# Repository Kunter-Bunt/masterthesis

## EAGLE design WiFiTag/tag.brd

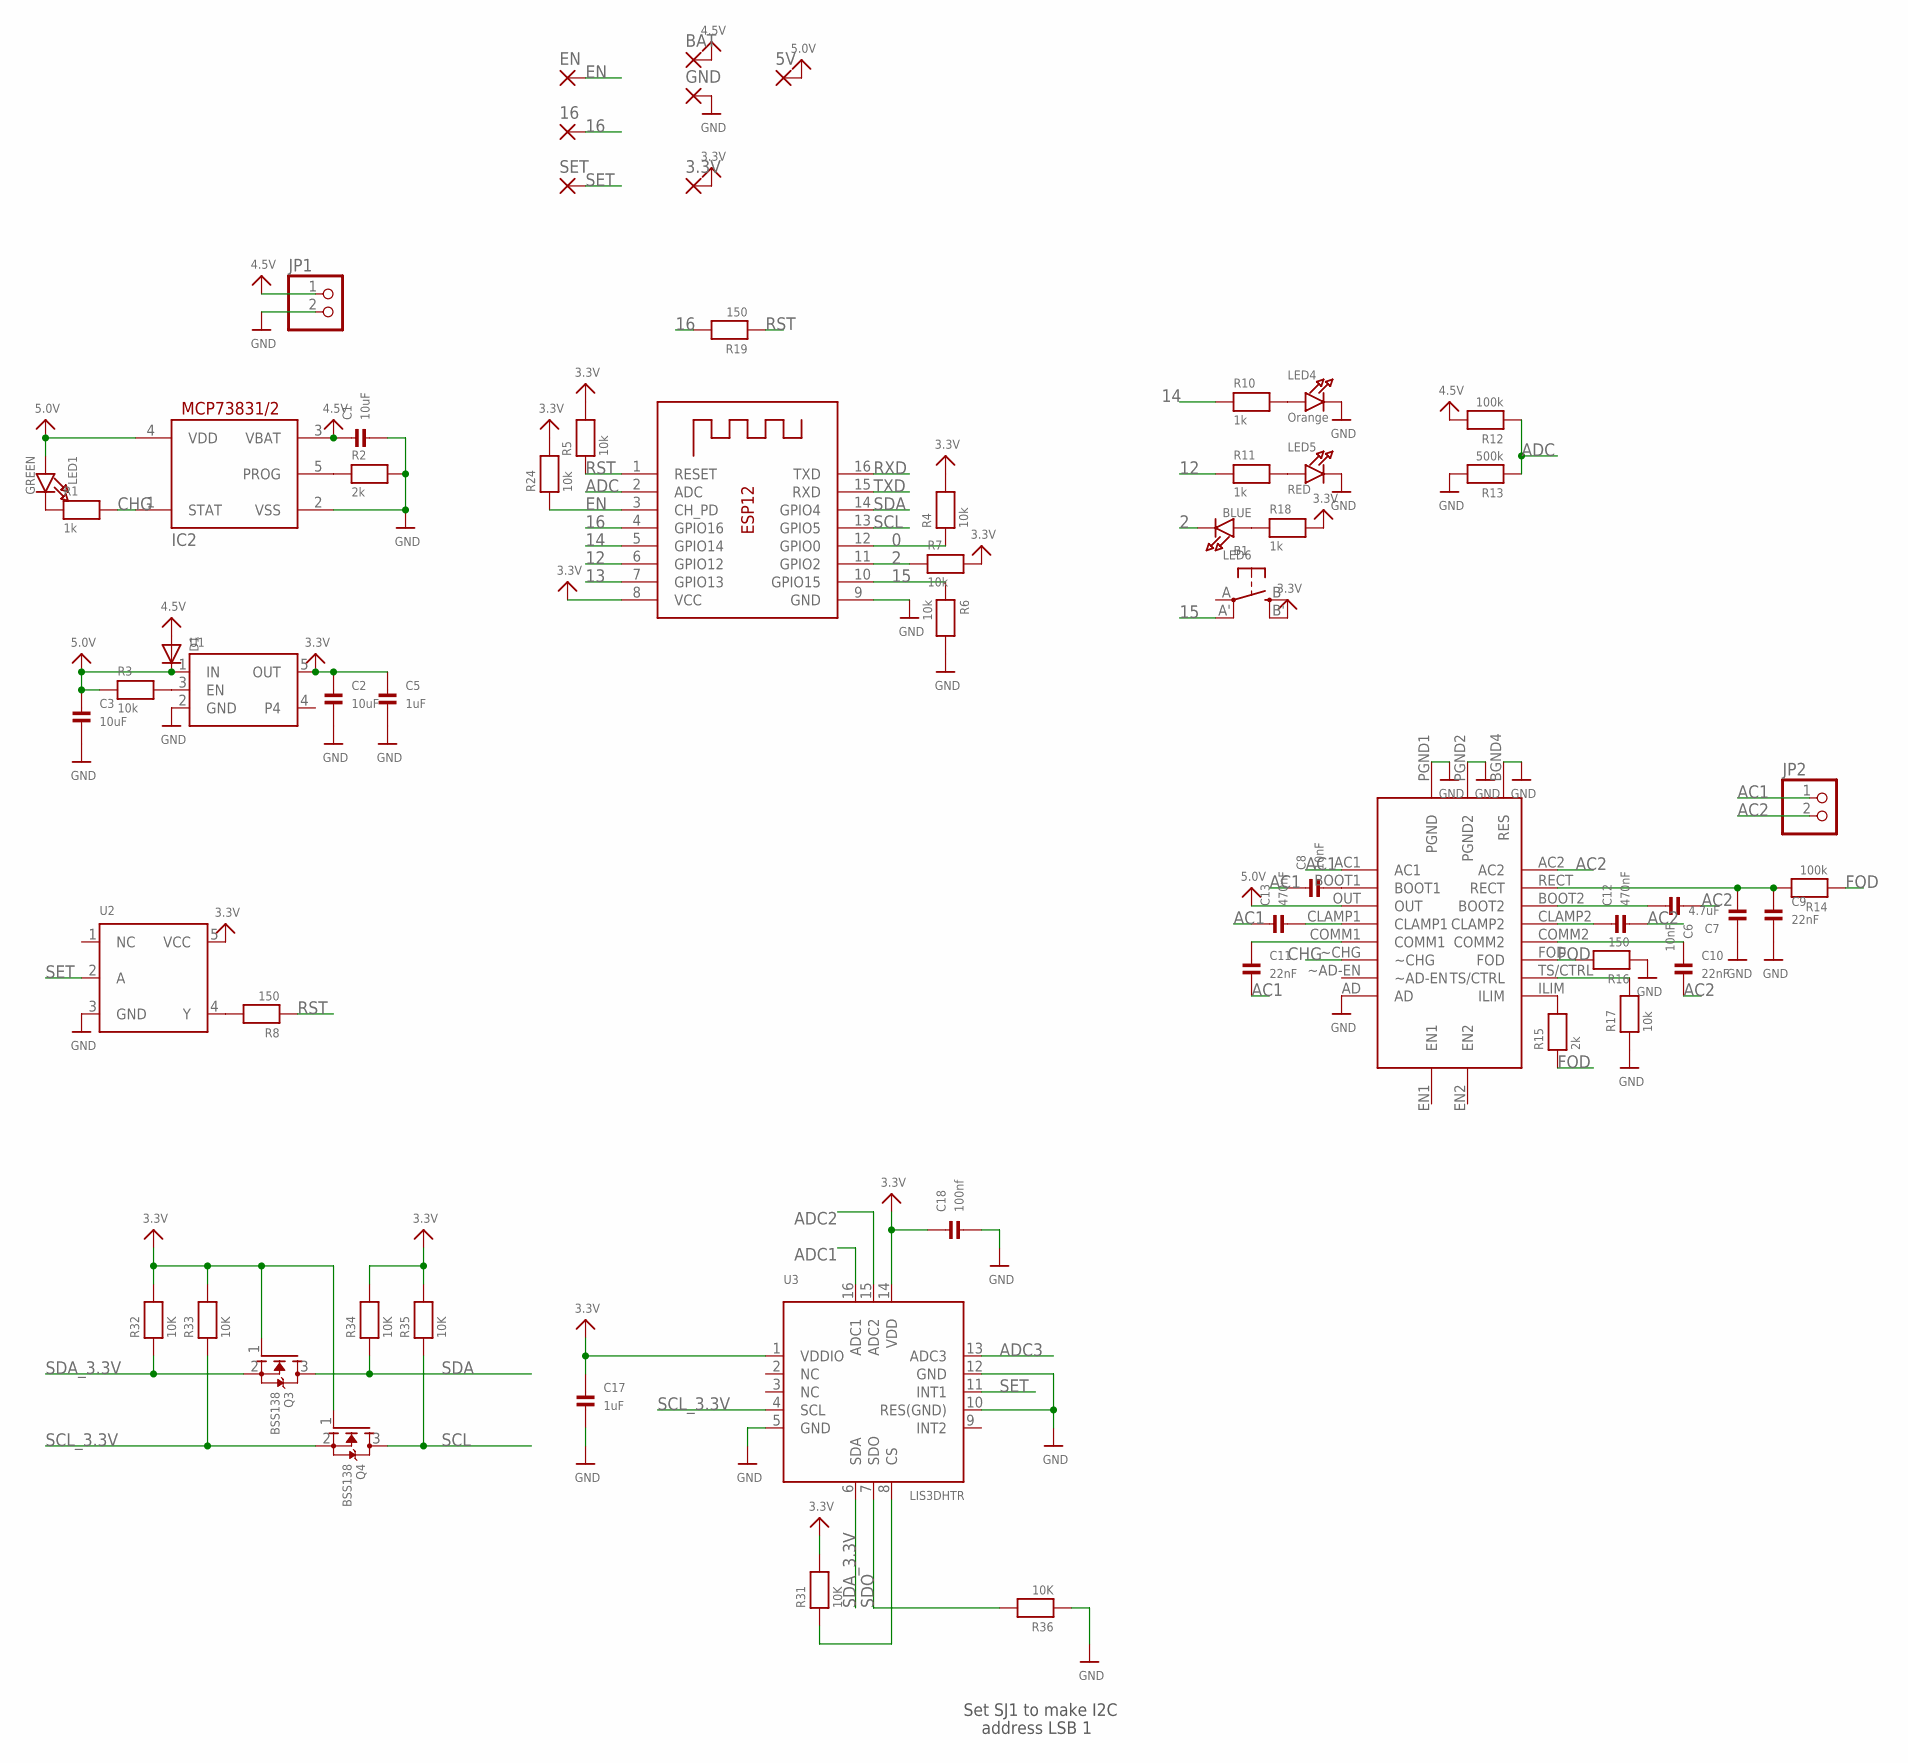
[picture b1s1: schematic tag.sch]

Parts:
3.3V, 5V, 16: SMD2; SMD1,27-2,54
B1: SWITCH_TACT_SMT4.6X2.8; BTN_KMR2_4.6X2.8
BAT: SMD2; SMD1,27-2,54
C1, C2, C3: 10uF; 0603
C5, C17: 1uF; 0402
C6, C8: 10nF; 0402
C7: 4.7uF; 0603
C9, C10, C11: 22nF; 0402
C12, C13: 470nF; 0402
C18: 100nf; 0402
D1: DIODESOD-123; SOD-123
EN: SMD2; SMD1,27-2,54
GND: SMD2; SMD1,27-2,54
IC2: MCP73831/OT; SOT23-5L
JP1, JP2: HEADER-1X2; 1X02_OVAL
LED1: GREEN; CHIPLED_0603
LED4: Orange; CHIPLED_0603
LED5: RED; CHIPLED_0603
LED6: BLUE; CHIPLED_0603
Q3, Q4: BSS138; SOT23-WIDE
R1, R10, R11, R18: 1k; 0402
R2, R15: 2k; 0402
R3, R4, R5, R6, R7, R17, R24: 10k; 0402
R8, R16, R19: 150; 0402
R12, R14: 100k; 0402
R13: 500k; 0402
R31, R32, R33, R34, R35, R36: 10K; 0402
SET: SMD2; SMD1,27-2,54
U1: VREG_SOT23-5; SOT23-5
U2: 74LVC1G04; SOT23-5
U3: LIS3DHTR; LGA16_3X3MM
U$1: BQ51013B; VQFN
X1: ESP-12

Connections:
0: R4.1, X1.12 (GPIO0)
2: LED6.C, R7.1, X1.11 (GPIO2)
3.3V: 3.3V.1, B1.B' (S1), C2.1, C5.1, C17.1, C18.1, Q3.1 (G), Q4.1 (G), R4.2, R5.2, R7.2, R18.2, R24.2, R31.2, R32.2, R33.2, R34.2, R35.2, U1.5 (OUT), U2.5 (VCC), U3.1 (VDDIO), U3.14 (VDD), X1.8 (VCC)
4.5V: BAT.1, C1.1, D1.A, IC2.3 (VBAT), JP1.1, R12.2
5.0V: 5V.1, C3.1, D1.C, IC2.4 (VDD), LED1.A, R3.1, U1.1 (IN), U$1.OUT
12: R11.1, X1.6 (GPIO12)
13: X1.7 (GPIO13)
14: R10.1, X1.5 (GPIO14)
15: B1.A' (P1), R6.1, X1.10 (GPIO15)
16: 16.1, R19.2, X1.4 (GPIO16)
AC1: C8.1, C11.2, C13.1, JP2.1, U$1.AC1
AC2: C6.1, C10.2, C12.2, JP2.2, U$1.AC2
ADC: R12.1, R13.1, X1.2 (ADC)
ADC1: U3.16 (ADC1)
ADC2: U3.15 (ADC2)
ADC3: U3.13 (ADC3)
CHG: IC2.1 (STAT), R1.2, U$1.~CHG
EN: EN.1, R24.1, X1.3 (CH_PD)
FOD: R14.1, R15.1, R16.2, U$1.FOD
GND: C1.2, C2.2, C3.2, C5.2, C7.1, C9.2, C17.2, C18.2, GND.1, IC2.2 (VSS), JP1.2, LED4.C, LED5.C, R2.2, R6.2, R13.2, R16.1, R17.1, R36.1, U1.2 (GND), U2.3 (GND), U3.5 (GND), U3.10 (RES(GND)), U3.12 (GND), U$1.AD, U$1.BGND4 (RES), U$1.PGND1 (PGND), U$1.PGND2, X1.9 (GND)
unnamed: C11.1, U$1.COMM1
unnamed: LED1.C, R1.1
unnamed: IC2.5 (PROG), R2.1
unnamed: LED6.A, R18.1
unnamed: R3.2, U1.3 (EN)
unnamed: R8.2, U2.4 (Y)
unnamed: R31.1, U3.8 (CS)
unnamed: LED4.A, R10.2
unnamed: LED5.A, R11.2
unnamed: C8.2, U$1.BOOT1
unnamed: C6.2, U$1.BOOT2
unnamed: C7.2, C9.1, R14.2, U$1.RECT
unnamed: R15.2, U$1.ILIM
unnamed: R17.2, U$1.TS/CTRL
unnamed: C10.1, U$1.COMM2
unnamed: C13.2, U$1.CLAMP1
unnamed: C12.1, U$1.CLAMP2
RST: R5.1, R8.1, R19.1, X1.1 (RESET)
RXD: X1.16 (TXD)
SCL: Q4.3 (D), R35.1, X1.13 (GPIO5)
SCL_3.3V: Q4.2 (S), R33.1, U3.4 (SCL)
SDA: Q3.3 (D), R34.1, X1.14 (GPIO4)
SDA_3.3V: Q3.2 (S), R32.1, U3.6 (SDA)
SDO: R36.2, U3.7 (SDO)
SET: SET.1, U2.2 (A), U3.11 (INT1)
TXD: X1.15 (RXD)

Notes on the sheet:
Set SJ1 to make I2C
address LSB 1

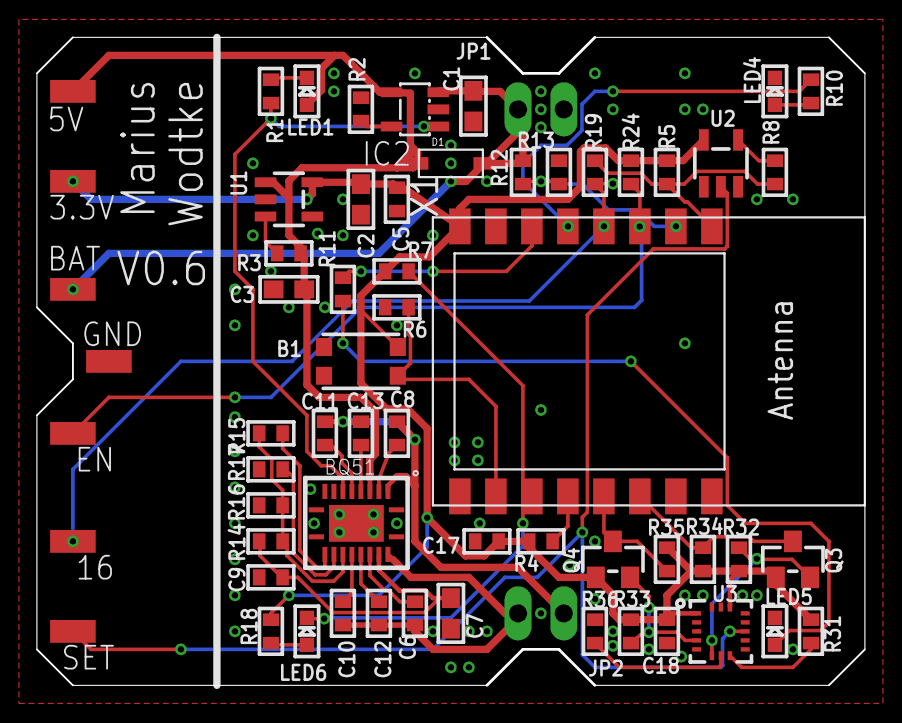
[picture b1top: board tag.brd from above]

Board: 2 copper layers, 46.0 x 36.0 mm, 62 parts (0 on the bottom side), 40 nets.

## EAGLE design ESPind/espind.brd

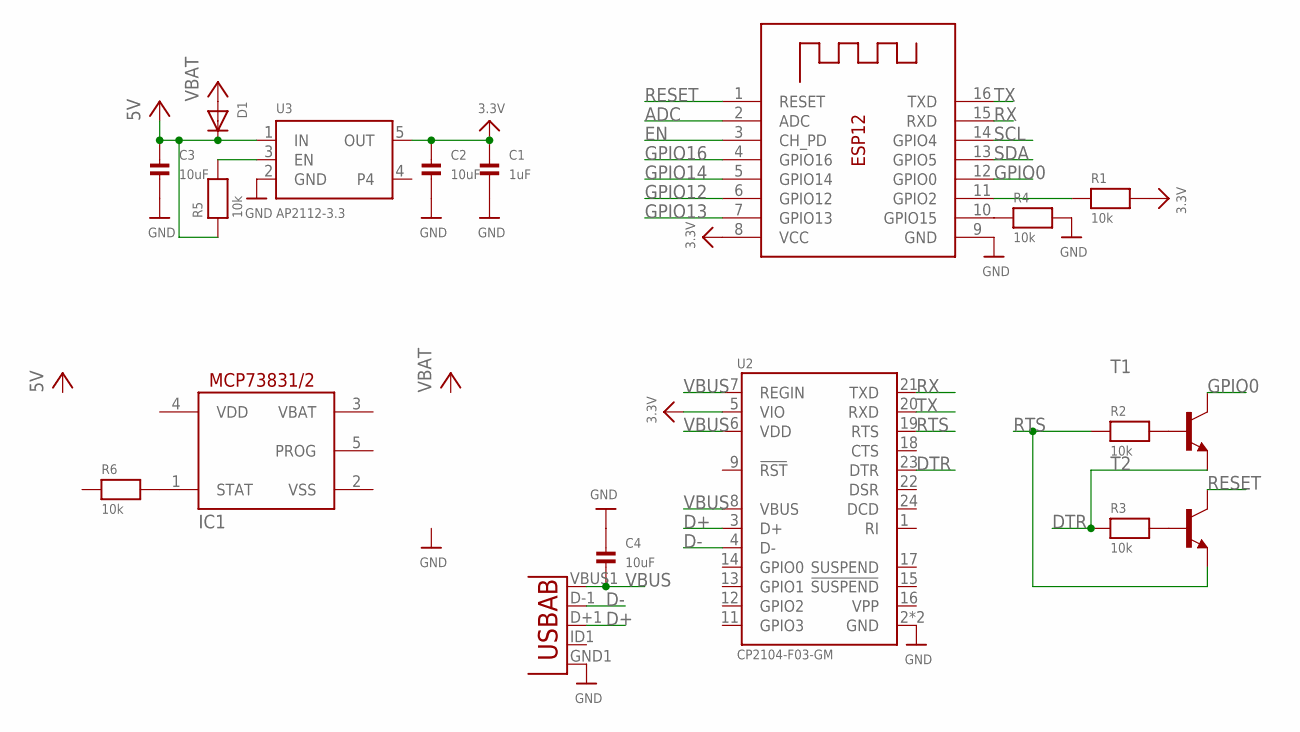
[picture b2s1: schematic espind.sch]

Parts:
C1: 1uF; 0402
C2, C3, C4: 10uF; 0402
D1: DIODESOD-123; SOD-123
IC1: MCP73831/OT; SOT23-5L
R1, R2, R3, R4, R5, R6: 10k; 0402
T1, T2: MMBT2222ALT1-NPN-SOT23-BEC; SOT23-BEC
U1: USB""; USB-MICRO-SMD
U2: CP2104-F03-GM; QFN-24-4X4
U3: AP2112-3.3; SOT23-5
X1: ESP-12

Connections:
ADC: X1.2 (ADC)
D+: U1.D+1 (D+), U2.3 (D+)
D-: U1.D-1 (D-), U2.4 (D-)
DTR: R3.1, T1.E, U2.23 (DTR)
EN: X1.3 (CH_PD)
GND: C1.2, C2.2, C3.2, C4.1, R4.2, U1.GND1 (GND), U2.2 (GND), U2.PAD (GND), U3.2 (GND), X1.9 (GND)
GPIO0: T1.C, X1.12 (GPIO0)
GPIO12: X1.6 (GPIO12)
GPIO13: X1.7 (GPIO13)
GPIO14: X1.5 (GPIO14)
GPIO16: X1.4 (GPIO16)
unnamed: R1.1, X1.11 (GPIO2)
unnamed: R4.1, X1.10 (GPIO15)
unnamed: R2.2, T1.B
unnamed: R3.2, T2.B
unnamed: R5.2, U3.3 (EN)
unnamed: IC1.1 (STAT), R6.2
RESET: T2.C, X1.1 (RESET)
RTS: R2.1, T2.E, U2.19 (RTS)
RX: U2.21 (TXD), X1.15 (RXD)
SCL: X1.14 (GPIO4)
SDA: X1.13 (GPIO5)
TX: U2.20 (RXD), X1.16 (TXD)
VBUS: C4.2, U1.VBUS1 (VBUS), U2.6 (VDD), U2.7 (REGIN), U2.8 (VBUS)
VCC: C1.1, C2.1, C3.1, D1.A, D1.C, R1.2, R5.1, U2.5 (VIO), U3.1 (IN), U3.5 (OUT), X1.8 (VCC)
VDD: IC1.4 (VDD)
VSS: IC1.2 (VSS)

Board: 2 copper layers, 18 parts (0 on the bottom side), 17 nets, no tracks yet.

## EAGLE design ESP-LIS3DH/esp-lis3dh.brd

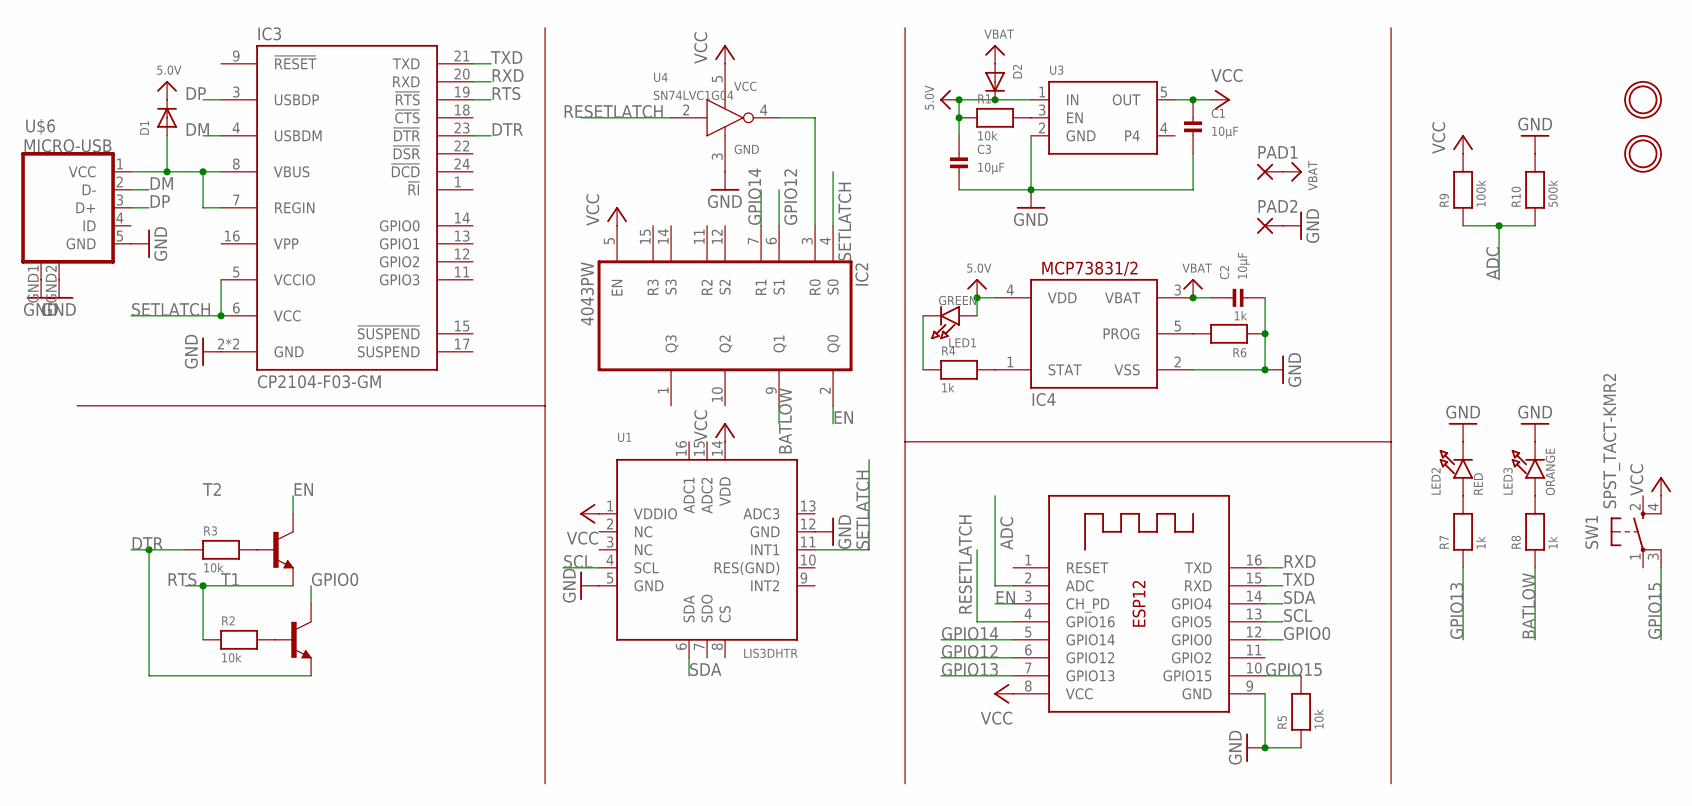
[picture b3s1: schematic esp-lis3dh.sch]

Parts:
C1, C2, C3: 10µF; 0805
D1, D2: DIODESOD-123; SOD-123
IC2: 4043PW; TSSOP16
IC3: CP2104-F03-GM; QFN24-PAD
IC4: MCP73831/OT; SOT23-5L
LED1: GREEN; CHIPLED_0805
LED2: RED; CHIPLED_0805
LED3: ORANGE; CHIPLED_0805
PAD1, PAD2: SMD2; SMD1,27-2,54
R1, R2, R3, R5: 10k; 0603
R4, R6, R7, R8: 1k; 0603
R9: 100k; 0603
R10: 500k; 0603
SW1: SPST_TACT-KMR2; KMR2
T1, T2: MMBT2222ALT1-NPN-SOT23-BEC; SOT23-BEC
U1: LIS3DHTR; LGA16_3X3MM
U3: VREG_SOT23-5; SOT23-5
U4: SN74LVC1G04; SOT23-5
U$6: MICRO-USB
U$7, U$8: MOUNTINGHOLE2.5; MOUNTINGHOLE_2.5_PLATED
X1: ESP-12

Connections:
5.0V: C3.1, D1.C, D2.C, IC4.4 (VDD), LED1.A, R1.1, U3.1 (IN)
ADC: R9.1, R10.1, X1.2 (ADC)
BATLOW: IC2.9 (Q1), R8.1
DM: IC3.4 (USBDM), U$6.2 (D-)
DP: IC3.3 (USBDP), U$6.3 (D+)
DTR: IC3.23 (!DTR), R3.1, T1.E
EN: IC2.2 (Q0), T2.C, X1.3 (CH_PD)
GND: C1.2, C2.2, C3.2, IC3.2 (GND), IC3.TP (GND), IC4.2 (VSS), LED2.C, LED3.C, PAD2.1, R5.1, R6.1, R10.2, U1.5 (GND), U1.12 (GND), U3.2 (GND), U4.3 (GND), U$6.5 (GND), U$6.GND1 (GND), U$6.GND2 (GND), X1.9 (GND)
GPIO0: T1.C, X1.12 (GPIO0)
GPIO12: IC2.6 (S1), X1.6 (GPIO12)
GPIO13: R7.1, X1.7 (GPIO13)
GPIO14: IC2.7 (R1), X1.5 (GPIO14)
GPIO15: R5.2, SW1.3 (P1), X1.10 (GPIO15)
unnamed: IC2.3 (R0), U4.4 (Y)
unnamed: IC4.5 (PROG), R6.2
unnamed: LED2.A, R7.2
unnamed: R1.2, U3.3 (EN)
unnamed: R2.2, T1.B
unnamed: IC4.1 (STAT), R4.2
unnamed: LED3.A, R8.2
unnamed: LED1.C, R4.1
unnamed: R3.2, T2.B
unnamed: D1.A, IC3.7 (REGIN), IC3.8 (VBUS), U$6.1 (VCC)
RESETLATCH: U4.2 (A), X1.4 (GPIO16)
RTS: IC3.19 (!RTS), R2.1, T2.E
RXD: IC3.20 (RXD), X1.16 (TXD)
SCL: U1.4 (SCL), X1.13 (GPIO5)
SDA: U1.6 (SDA), X1.14 (GPIO4)
SETLATCH: IC2.4 (S0), IC3.5 (VCCIO), IC3.6 (VCC), U1.11 (INT1)
TXD: IC3.21 (TXD), X1.15 (RXD)
VBAT: C2.1, D2.A, IC4.3 (VBAT), PAD1.1
VCC: C1.1, IC2.5 (EN), IC2.16 (VDD), R9.2, SW1.4 (S1), U1.1 (VDDIO), U1.14 (VDD), U3.5 (OUT), U4.5 (VCC), X1.8 (VCC)
VPP: IC3.16 (VPP)
VSS: IC2.8 (VSS)

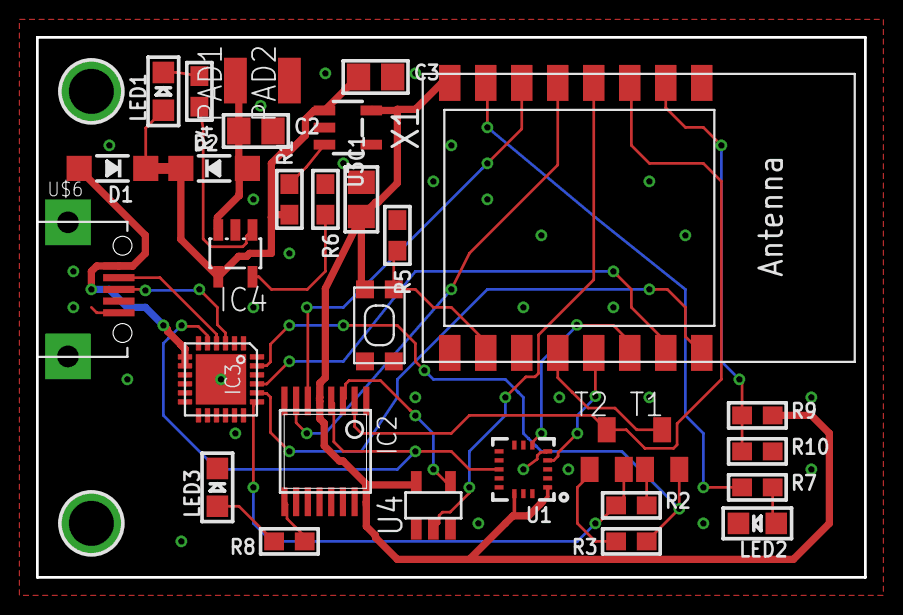
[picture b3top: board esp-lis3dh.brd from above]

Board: 2 copper layers, 46.0 x 30.0 mm, 33 parts (0 on the bottom side), 32 nets.

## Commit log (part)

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2016-12-12 Initial commit with a simple blinking sketch for ESP 8266
2016-12-14 added sketch with probe request utility
2017-01-24 Added a hello world server c++ project
2017-01-26 added script for listening to probe requests
2017-02-13 added tshark tutorial and esptool with working blinking script (tested)
2017-02-15 added a sketch that should produce beacon frames (untested)
2017-02-15 modified probereq sketch to get desired functionality & added new fields for bssid on the tshark script
2017-02-17 Added support for single device monitoring on shark.sh
2017-02-17 Got rid of setup code to reduce power consumption
2017-02-17 Added sketch for quick testing battery life with loads of probe requests
2017-02-20 renamed Spam sketch to differentiate between channel iteration and random channel
2017-02-20 New sketch that handles Request spam with random channel
2017-02-21 Added support for reading files from the arguments
2017-02-21 server now takes multiple file arguments and prints them like cat, but also works for streams, pipe output of commands to it with <(command), one thread per file, added thread support in makefile
2017-03-09 minor changes to sketches for testing
2017-03-09 Annotations and debugging for server.cpp
2017-04-09 Deleted flashing script and added a tutorial instead
2017-04-09 Changed blinky Makefile so that flashing works correctly
2017-04-11 Optimized tag on-time to 0.22s and added comments for the diferent parts of the packet sent
2017-04-11 Continued annotating packet
2017-04-11 cleaned off unnecessary imports
2017-04-11 forgot to save, cleaned imports
2017-04-14 Added programm for spamming, shortened packet to an absolute minimum, both the original and shorted are conserved in packet versions
2017-04-14 added the wisdoc template for the written thesis
2017-04-14 added the Makefile for probeReqSpam
2017-04-15 Added the papers to the bibtex file
2017-04-15 replaced shark.sh with two seperate scripts to avoid giving root priviliges to tshark, setup still needs sudo
2017-04-15 prepared spam for the second test run
2017-04-15 Deleted esptool contents, esp-open-sdk shall be used
2017-04-17 Started the Thesis with the sections Zeilsetzung and Anforderungen
2017-04-18 Added a Motivation and Gliederung to the thesis
2017-04-18 Added working sketch for a naiveTag for battery comparison
2017-04-21 Small corrections and rewriting in einleitung
2017-04-21 Added a sketch which is able to read the Vcc_in of the ESP
2017-04-21 No major changes, just attributet them to non admin editing
2017-04-21 Started the section Klassifikation von Ortungssystemen
2017-04-22 More on Klassifikation
2017-04-22 More Klassifikation
2017-05-08 Added a sketch that can read values and interrupts from LISD3H
2017-05-08 Added a sketch that turns a MOSFET on and of to control a current flow
2017-05-08 VccRead now properly reads the battery, cant read bat and chip vcc at the same time!
2017-05-08 Switching the network and cleaned up unnecessary code
2017-05-08 Switched to the short packet
2017-05-08 Completed the Klassifikation and added a new chapter for Vorherige Arbeiten
2017-05-08 Wrote on vorherige and changed Selbst-Lokalisation to Selbstlokalisation, added RADAR papers to the bib
2017-05-10 Wrote on Vorherige Arbeiten, properly added it to the Thesis
2017-05-11 Further on Vorherige
2017-05-11 Added light sleep to naiveTag to reduce power consumption
2017-05-11 Added new sketch for the implementation of the RADAR tag
2017-05-15 Added deviceless localization to Vorherige Arbeiten and a placeholder for Bluetooth-Localization
2017-05-15 Started new chapter Hrdware und Programmierung
2017-05-15 Speeling errors
2017-05-16 Added subsections for ekahau and aeroscout, excluded the hardprog chapter for submission
2017-05-17 spellchecking on Vorherige
2017-05-17 Added an implementation for a RADAR-like Tag
2017-05-19 Added an implementation for the naiveTag
2017-05-19 optimized the RADARTAg for efficiency
2017-05-22 Cleaned up imports on naiveTag
2017-05-22 Added sketch for the WiFiLLS Tag
2017-05-22 Added implementation for the WiFiLLS Tag
2017-05-23 Fixed some bugs and optimized WiFiLLSTag
2017-05-23 Activated the Lightsleep on WiFILLS Tags
2017-05-24 Startet Grundlagen in noChanges
2017-05-29 Started writing about ESP and the programming possibilities
2017-05-29 Completed the subsection open sdk
2017-05-30 Added a section for the wifills tag implementattion
2017-05-30 Started the section for the naiveTag
2017-05-31 Further on noChanges, pretty much finished
2017-05-31 Added new chapter softwareChanges
2017-05-31 Shortened down the message of RADAR Tag for a fair comparasion, did not yield an improvement
2017-05-31 Further on softwareChanges, some corrections in others
2017-05-31 naiveTag now sends 3 UDPs for safety
2017-06-01 Added citations for phase 1/2
2017-06-01 Added a safety intervall fpr naiveTag
2017-06-02 Added the titlepage and notification
2017-06-02 Spellchecking
2017-06-05 Added a server that accepts and print tcp data, client.py is for testing it
2017-06-05 Added a naiveTag that uses tcp, it is lokated in a new folder because it required a completely new code basis
2017-06-05 Shrinked the probeReq packed buffer to save Memory
2017-06-07 tcpTag got its keepalive back, setup got +x
2017-06-07 Additions to the tables with testing results
2017-06-10 Changes on naiveTag for retests
2017-06-10 Added smart tag functionality to probeReq
2017-06-10 Minor changes, VccRead now reads a button too
2017-06-10 Completed tables on optimized associationTag
2017-06-12 Integrated esp-open-sdk into the project, successfully tested
2017-06-15 Spellchecking on noChanges
2017-06-16 Spellchecking finished
2017-06-20 Started new chapter hardwareChanges
2017-06-20 Additions to bib for hardwareChanges chapter
2017-06-20 Added the chapter hardwareChanges to the thesis, label correction in softwareChanges
2017-06-20 Started literature overview in hardwareChanges
2017-06-23 Restructured document, started on bluetooth basics
2017-06-23 Further on bluetooth
2017-06-25 Added some explanation about linear voltage regulators and updated text accordingly
2017-06-25 Added a section about irr bluetooth paper
2017-06-26 Added sections about inquiry localisation and topology in analyse
2017-07-05 Prepared RADAR Tag Implementation for range testing
2017-07-05 Added autoconnect to WifiLLS
2017-07-05 Added autoconnect to probeReq
2017-07-05 Changed behavior of tcpNaiveTag to sending the SP MAC when connecting
2017-07-05 Changed server.py to python3
2017-07-05 Added a probeReq Tag that can receive alarms through beacons
2017-07-05 Changed accelint for easy threshhold manipulation
2017-07-05 Changed probeReq paket for short version
2017-07-05 Added sketch that advertises the BLE Feather
2017-07-05 Started on the comments from Kai
2017-07-07 Added new chapter about the range tests
2017-07-07 Changed the chapter titles
2017-07-07 Added section about nrf52
2017-07-07 Added scripts for scanning bluetooth low energy
2017-07-08 Added wifi dropout to tcptag
2017-07-08 Further on bluetooth implementation
2017-07-08 Modified the blebeacon for 1 sec operation
2017-07-08 Modified server to work with lancom ap
2017-07-08 Changed Knoten to Basisstation
2017-07-09 Some new sections to the lower chapters
2017-07-10 Added subsection für nodeless topologies
2017-07-10 Added new chapter for realworld tests, added referencing label to nochanges
2017-07-10 Further on realworld, added labels to other chapters
2017-07-17 Hotspot script activates and deactivates hotspot in predicttable mesaure
2017-07-17 added sketches for LoRa testing
2017-07-17 Changed the tables in softwareChanges
2017-07-17 Added the Feather componenets to the power calculation
2017-07-17 Added some decriptive introductions to verwandte Arbeiten
2017-07-17 Added the missing references
2017-07-17 Changed the Gliederung to accomidate new chapters, dadded references to the bib
2017-07-17 New chapter for accelerometer
2017-07-17 New chaptr fazit
2017-07-17 Changed the power class table, added citations
2017-07-17 Added several images
2017-07-17 Added functionality to setup.sh to kill wifi by itself
2017-07-17 Added a oneplus probereq packet to packet versions, probeReq Tag now uses this one
2017-08-03 Added new python servers for ProbeReq parsing. lanserver encodes Probe Requests, dbserver decodes them
2017-08-03 Added some pictures to the thesis
2017-08-06 Added passages and images for LoRa
2017-08-06 Minor changes to the servers reganding the codebook
2017-08-06 Batch commit for tags
2017-08-09 Added the resource icons for the ipes
2017-08-09 Added theoretical consumption for lora
2017-08-15 Added grundlagen and pictures for lora
2017-08-15 Started on Kais comments, renamed Abb. to Abbildung chenged pictures of tables to Tabellen etc
2017-08-18 Added a sketch for measuring current with INA
2017-08-18 Changed the packet back to minimal
2017-08-23 Added Power Consumption data
2017-08-23 Added a sket that does low power lora sending
2017-08-23 multiple chages to esp programms for testing power consumption
2017-08-23 added low power support for ble
2017-08-23 Added a sket that reads the ina219
2017-08-23 visualized the power consumtion data
2017-08-23 Added descrisptions for tests, no pictures or tables yet
2017-08-24 Added plots to the thesis
2017-08-24 added the tables to realworld
2017-08-25 Added more plots
2017-08-29 First round of spell checking
2017-08-30 second round of spellchecking
2017-08-30 Reargumetation, added section about chosen hardware and the methods
2017-08-30 Split hardwarechanges into two chapters
2017-08-30 Changed the introductions to match the new argumentation
2017-08-30 New chapter fazit
2017-08-31 Added multiple pictures to the thesis
2017-08-31 moved the chapter lis3dh into the probereq chapter
2017-09-03 emph on special expressions, - on germanization
2017-09-06 Added the section about no ap
2017-09-06 Started the fazit
2017-09-07 further on fazit
2017-09-07 Changed the lora results and changed picture style
2017-09-07 the new result csvs for lora
2017-09-11 Started with the presentation
2017-09-12 Presentation up until RADAR
2017-09-14 Changed Ortungsserver to Ortungsdienst
2017-09-15 Lots of spell checking, changed structure of Auswahl, changed table spaces
2017-09-19 Added an overview for consumptions
2017-09-19 Added some smaller section (Fazit, Problemstellung) and changed some spelling
2017-09-19 New round of spellchecking
2017-09-20 noap got overlap, plotter now plots in seconds
2017-09-20 Added a nomalization to power readings
2017-09-20 Batch commit
2017-09-22 Changed the programming instructions
2017-09-25 lanserver now implements inteded parsing, no server sindig or quality checks
2017-09-26 lanserver now sends data to dbserver, changed rssi finding, logs for reference
2017-09-28 Worked on Kais Comments
2017-10-01 First round of spellchecking with devorie
2017-10-02 Second roud of devories comments
2017-10-02 Further on presentation
2017-10-06 Changed the topology section, now the pictrues are between the text
2017-10-27 Michaels comments
2017-10-27 Kais comments on beamer
2017-10-27 Started hardware design
2017-10-31 Added libraries for eagle
2017-10-31 Changed s to Sekunden
2017-11-01 Spell checking round -um zu-
2017-11-02 changed meter to m
2017-11-08 Spell checking
2017-11-14 Small mistake in TDOA and added backup to beamer
2017-11-15 Worked on pcb
2017-11-15 Added the Gehäuse
2017-11-30 Worked on prototype
2017-11-30 Gerbers for prototype
2017-11-30 Inductive charging prototype start
2017-11-30 libraries for eagle
2017-11-30 Comments from Andreas
2017-11-30 Further on Andreas Comments
2017-11-30 Changed the Title page accordingly
2017-11-30 New title picture for presentation
2017-12-16 Changed the last slide diagramm from bar- to scatterplot
2017-12-16 NEW TAG PCB
2018-01-07 Hopefully final presentation
2018-01-07 New RESTServer to display information
2018-01-07 3 Gehäuse printed version
2018-02-24 New board version 0.3
2018-02-24 Last change to the tile page, wrong departmant
2018-02-24 New case
2018-03-17 WifiTagV0.4
2018-04-14 new tag version 0.5
2018-04-27 XNOR Tag version
2018-05-01 Added submodule
2018-06-02 V06 of PCB
2018-06-02 New Gehäuse version

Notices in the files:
parts and their libraries:
microbuilder: This work is placed in the public domain, and may be freely used for commercial and non-commercial work with the following conditions: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
